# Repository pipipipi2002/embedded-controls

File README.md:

# The Hardware
- [Interactive BOM](https://pipipipi2002.github.io/embedded-controls/hardware/controls-carier-board/output/interactive_bom.html)

## MCU
This sensor module will require the STM32F446VETx Module from [stm32f446vetx-dev-module](https://github.com/pipipipi2002/stm32f446vetx-dev-module)

## Sensor
No | Sensor | Description | Connection
---| --- |--- | ---
1  | ICM-40609-D | 6-axis IMU | SPI1
2  | ICM-42688-P | 6-axis IMU | SPI3
3  | BNO085      | 9-axis IMU | SPI2
4  | BMP390      | Barometer  | SPI4

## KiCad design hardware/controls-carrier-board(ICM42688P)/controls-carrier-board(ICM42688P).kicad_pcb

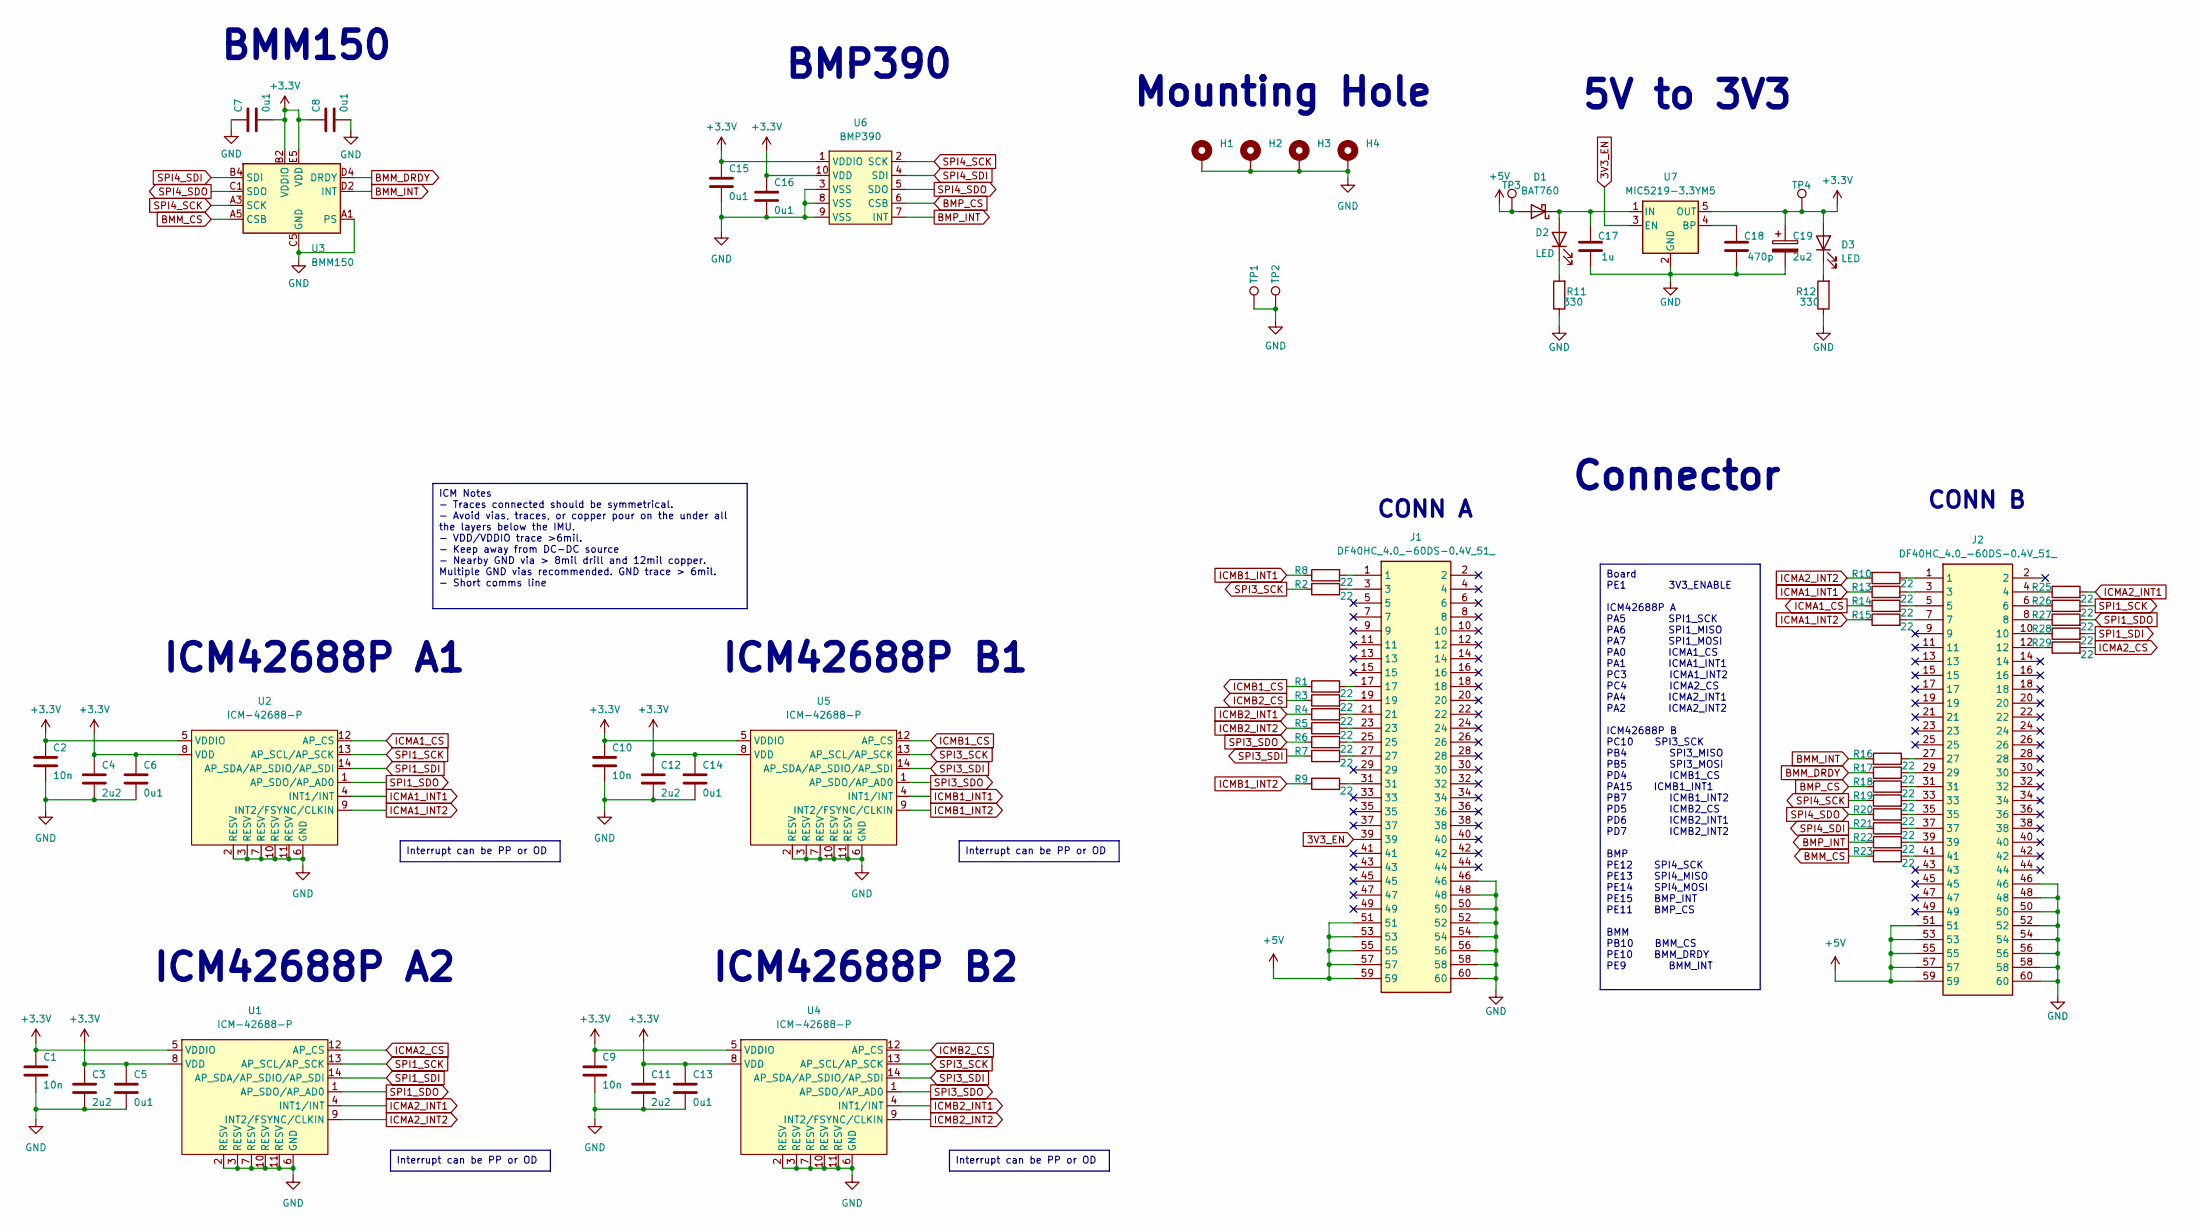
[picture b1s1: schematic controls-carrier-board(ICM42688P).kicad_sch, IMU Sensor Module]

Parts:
C1, C2, C9, C10: 10n; C_0402_1005Metric; JLCPCB C361206
C3, C4, C11, C12: 2u2; C_0402_1005Metric; JLCPCB C368595
C5, C6, C7, C8, C13, C14, C15, C16: 0u1; C_0402_1005Metric; JLCPCB C432917
C17: 1u; C_0603_1608Metric; JLCPCB C5673
C18: 470p; C_0603_1608Metric; JLCPCB C519409
C19: 2u2; CP_EIA-3216-18_Kemet-A_Pad1.58x1.35mm_HandSolder; JLCPCB C600494
D1: BAT760; D_SOD-323; JLCPCB C124187
D2, D3: LED; LED_0603_1608Metric; JLCPCB C131281
H1, H2, H3, H4: MountingHole_Pad; MountingHole_2.7mm_M2.5_Pad_Via
J1, J2: DF40HC_4.0_-60DS-0.4V_51_; DF40HC4060DS04V51; Mouser Part Number 798-DF4HC4060DS04V51
R1, R2, R3, R4, R5, R6, R7, R8, R9, R10, R13, R14, R15, R16, R17, R18, R19, R20, R21, R22, R23, R25, R26, R27, R28, R29: 22; R_0402_1005Metric; JLCPCB C413049
R11, R12: 330; R_0603_1608Metric; JLCPCB C441887
TP1, TP2, TP3, TP4: TestPoint; TestPoint_Keystone_5000-5004_Miniature
U1, U2, U4, U5: ICM-42688-P; ICM_LGA-14_3x2.5mm_P0.5mm; JLCPCB C1850418
U3: BMM150; WLCSP-12_1.56x1.56mm_P0.4mm; JLCPCB C171681
U6: BMP390; Bosch_LGA-10_2x2mm_P0.50mm; JLCPCB C9900016584
U7: MIC5219-3.3YM5; SOT-23-5; JLCPCB C29613

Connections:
3V3_EN: J1.39, U7.3 (EN)
+3.3V: C1.1, C2.1, C3.1, C4.1, C5.1, C6.1, C7.2, C8.1, C9.1, C10.1, C11.1, C12.1, C13.1, C14.1, C15.1, C16.1, C19.1, D3.2 (A), TP4.1, U1.5 (VDDIO), U1.8 (VDD), U2.5 (VDDIO), U2.8 (VDD), U3.B2 (VDDIO), U3.E5 (VDD), U4.5 (VDDIO), U4.8 (VDD), U5.5 (VDDIO), U5.8 (VDD), U6.1 (VDDIO), U6.10 (VDD), U7.5 (OUT)
+5V: D1.2 (A), J1.51, J1.53, J1.55, J1.57, J1.59, J2.51, J2.53, J2.55, J2.57, J2.59, TP3.1
BMM_CS: R23.1, U3.A5 (CSB)
BMM_DRDY: R17.1, U3.D4 (DRDY)
BMM_INT: R16.1, U3.D2 (INT)
BMP_CS: R18.1, U6.6 (CSB)
BMP_INT: R22.1, U6.7 (INT)
GND: C1.2, C2.2, C3.2, C4.2, C5.2, C6.2, C7.1, C8.2, C9.2, C10.2, C11.2, C12.2, C13.2, C14.2, C15.2, C16.2, C17.2, C18.2, C19.2, H1.1, H2.1, H3.1, H4.1, J1.46, J1.48, J1.50, J1.52, J1.54, J1.56, J1.58, J1.60, J2.46, J2.48, J2.50, J2.52, J2.54, J2.56, J2.58, J2.60, R11.1, R12.1, TP1.1, TP2.1, U1.2 (RESV), U1.3 (RESV), U1.6 (GND), U1.7 (RESV), U1.10 (RESV), U1.11 (RESV), U2.2 (RESV), U2.3 (RESV), U2.6 (GND), U2.7 (RESV), U2.10 (RESV), U2.11 (RESV), U3.A1 (PS), U3.C5 (GND), U3.E1 (GND), U3.E3 (GND), U4.2 (RESV), U4.3 (RESV), U4.6 (GND), U4.7 (RESV), U4.10 (RESV), U4.11 (RESV), U5.2 (RESV), U5.3 (RESV), U5.6 (GND), U5.7 (RESV), U5.10 (RESV), U5.11 (RESV), U6.3 (VSS), U6.8 (VSS), U6.9 (VSS), U7.2 (GND)
ICMA1_CS: R14.1, U2.12 (AP_CS)
ICMA1_INT1: R13.1, U2.4 (INT1/INT)
ICMA1_INT2: R15.1, U2.9 (INT2/FSYNC/CLKIN)
ICMA2_CS: R29.2, U1.12 (AP_CS)
ICMA2_INT1: R25.2, U1.4 (INT1/INT)
ICMA2_INT2: R10.2, U1.9 (INT2/FSYNC/CLKIN)
ICMB1_CS: R1.1, U5.12 (AP_CS)
ICMB1_INT1: R8.1, U5.4 (INT1/INT)
ICMB1_INT2: R9.1, U5.9 (INT2/FSYNC/CLKIN)
ICMB2_CS: R3.1, U4.12 (AP_CS)
ICMB2_INT1: R4.1, U4.4 (INT1/INT)
ICMB2_INT2: R5.1, U4.9 (INT2/FSYNC/CLKIN)
unnamed: C17.1, D1.1 (K), D2.2 (A), U7.1 (IN)
unnamed: D2.1 (K), R11.2
unnamed: D3.1 (K), R12.2
unnamed: J1.1, R8.2
unnamed: J1.3, R2.2
unnamed: J1.17, R1.2
unnamed: J1.19, R3.2
unnamed: J1.21, R4.2
unnamed: J1.23, R5.2
unnamed: J1.25, R6.2
unnamed: J1.27, R7.2
unnamed: J1.31, R9.2
unnamed: J2.1, R10.1
unnamed: J2.3, R13.2
unnamed: J2.4, R25.1
unnamed: J2.5, R14.2
unnamed: J2.6, R26.1
unnamed: J2.7, R15.2
unnamed: J2.8, R27.1
unnamed: J2.10, R28.1
unnamed: J2.12, R29.1
unnamed: J2.27, R16.2
unnamed: J2.29, R17.2
unnamed: J2.31, R18.2
unnamed: J2.33, R19.2
unnamed: J2.35, R20.2
unnamed: J2.37, R21.2
unnamed: J2.39, R22.2
unnamed: J2.41, R23.2
unnamed: C18.1, U7.4 (BP)
SPI1_SCK: R26.2, U1.13 (AP_SCL/AP_SCK), U2.13 (AP_SCL/AP_SCK)
SPI1_SDI: R28.2, U1.14 (AP_SDA/AP_SDIO/AP_SDI), U2.14 (AP_SDA/AP_SDIO/AP_SDI)
SPI1_SDO: R27.2, U1.1 (AP_SDO/AP_AD0), U2.1 (AP_SDO/AP_AD0)
SPI3_SCK: R2.1, U4.13 (AP_SCL/AP_SCK), U5.13 (AP_SCL/AP_SCK)
SPI3_SDI: R7.1, U4.14 (AP_SDA/AP_SDIO/AP_SDI), U5.14 (AP_SDA/AP_SDIO/AP_SDI)
SPI3_SDO: R6.1, U4.1 (AP_SDO/AP_AD0), U5.1 (AP_SDO/AP_AD0)
SPI4_SCK: R19.1, U3.A3 (SCK), U6.2 (SCK)
SPI4_SDI: R21.1, U3.B4 (SDI), U6.4 (SDI)
SPI4_SDO: R20.1, U3.C1 (SDO), U6.5 (SDO)

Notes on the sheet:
Board PE1 3V3_ENABLE ICM42688P A PA5 SPI1_SCK PA6 SPI1_MISO PA7 SPI1_MOSI PA0 ICMA1_CS PA1 ICMA1_INT1 PC3 ICMA1_INT2 PC4 ICMA2_CS PA4 ICMA2_INT1 PA2 ICMA2_INT2 ICM42688P B PC10 SPI3_SCK PB4 SPI3_MISO PB5 SPI3_MOSI PD4 ICMB1_CS PA15 ICMB1_INT1 PB7 ICMB1_INT2 PD5 ICMB2_CS PD6 ICMB2_INT1 PD7 ICMB2_INT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
ICM Notes - Traces connected should be symmetrical. - Avoid vias, traces, or copper pour on the under all the layers below the IMU. - VDD/VDDIO trace >6mil. - Keep away from DC-DC source - Nearby GND via > 8mil drill and 12mil copper. Multiple GND vias recommended. GND trace > 6mil. - Short comms l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
Interrupt can be PP or OD
Connector
5V to 3V3
BMM150
ICM42688P B1
Mounting Hole
ICM42688P A2
ICM42688P B2
BMP390
CONN A
ICM42688P A1
CONN B

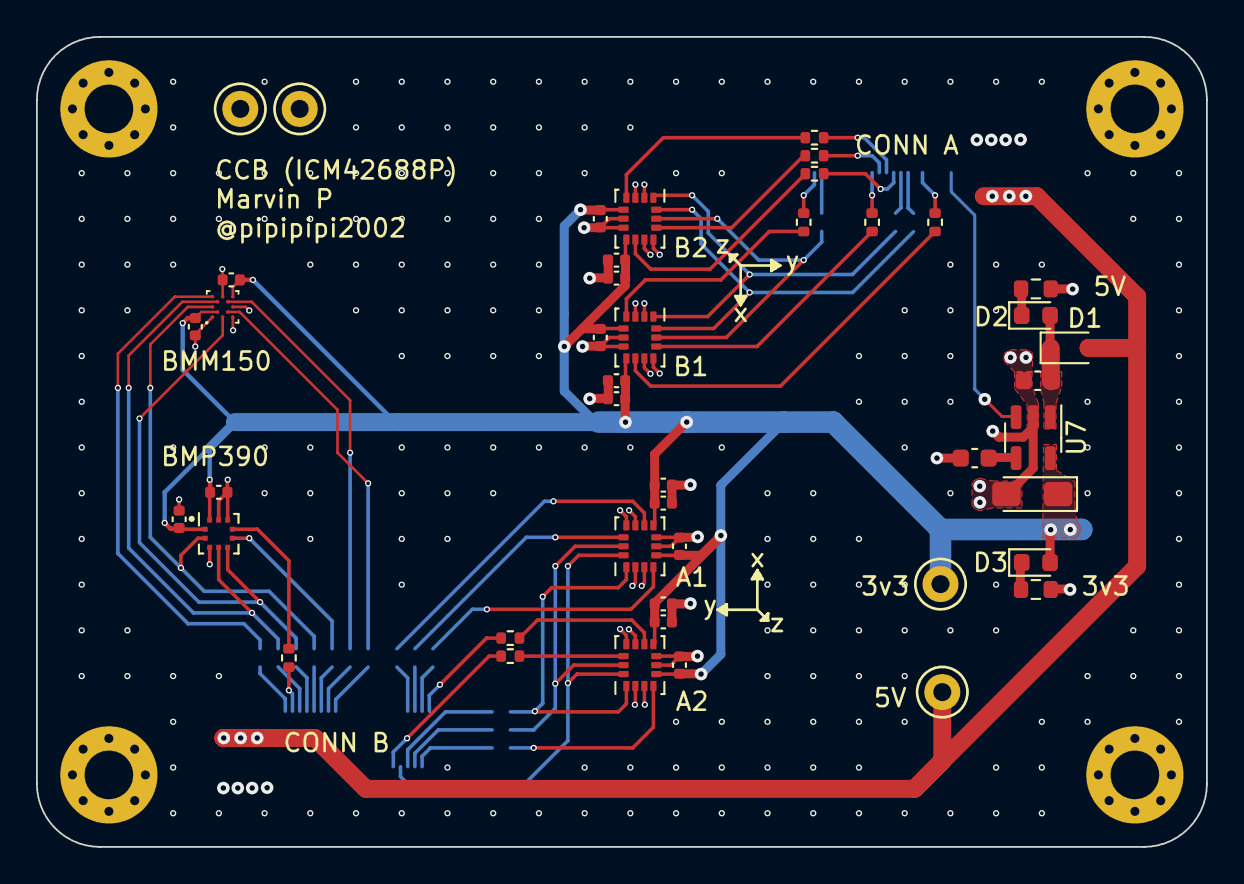
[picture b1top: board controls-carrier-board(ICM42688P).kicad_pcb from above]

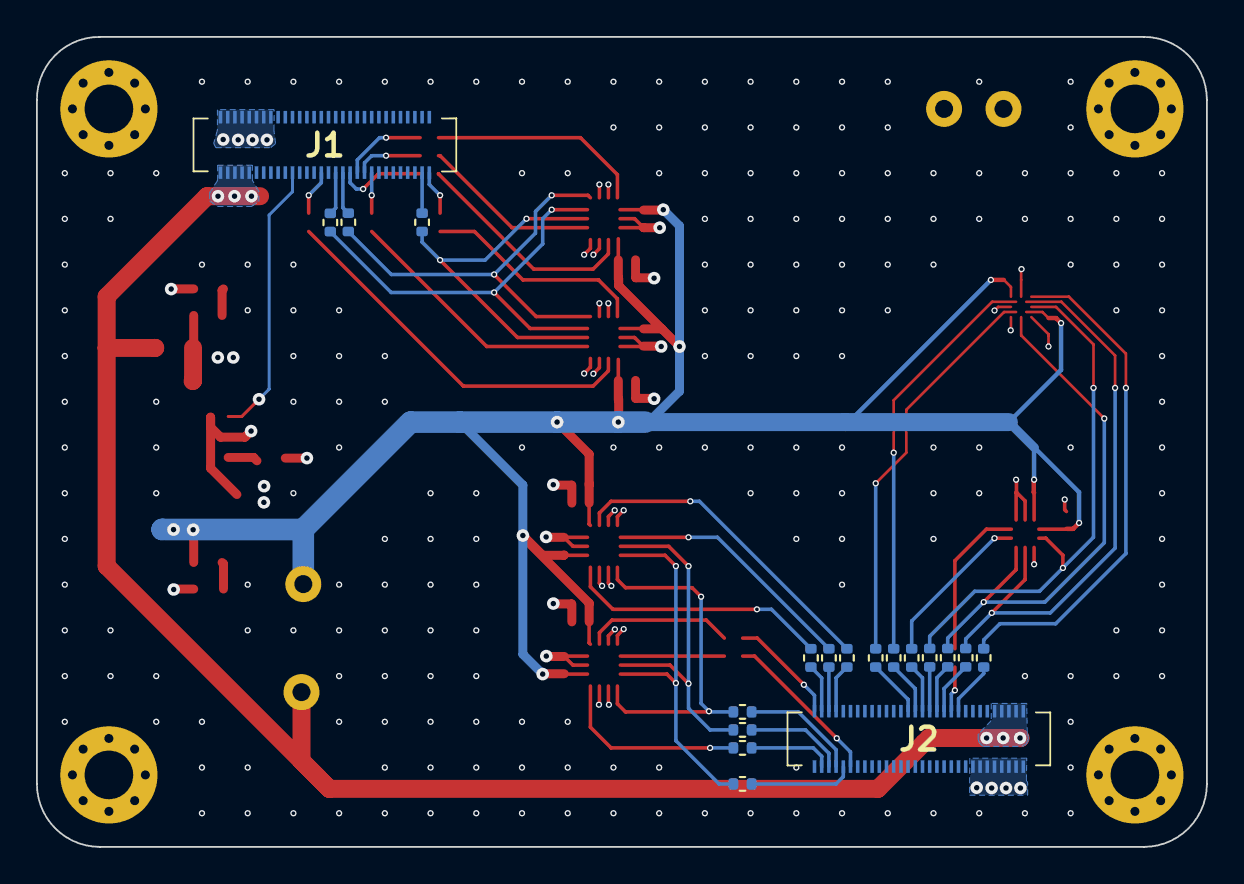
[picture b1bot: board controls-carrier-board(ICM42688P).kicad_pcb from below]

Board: 4 copper layers, 65.0 x 45.0 mm, 67 parts (19 on the bottom side), 60 nets.

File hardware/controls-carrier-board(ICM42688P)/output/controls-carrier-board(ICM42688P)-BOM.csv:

Comment,Designator,Footprint,LCSC
"10n","C1,C2,C9,C10","Capacitor_SMD:C_0402_1005Metric","C361206"
"1u","C17","Capacitor_SMD:C_0603_1608Metric","C5673"
"470p","C18","Capacitor_SMD:C_0603_1608Metric","C519409"
"2u2","C19","Capacitor_Tantalum_SMD:CP_EIA-3216-18_Kemet-A_Pad1.58x1.35mm_HandSolder","C600494"
"2u2","C3,C4,C11,C12","Capacitor_SMD:C_0402_1005Metric","C368595"
"0u1","C5,C6,C7,C8,C13,C14,C15,C16","Capacitor_SMD:C_0402_1005Metric","C432917"
"BAT760","D1","Diode_SMD:D_SOD-323","C124187"
"LED","D2,D3","LED_SMD:LED_0603_1608Metric","C131281"
"DF40HC_4.0_-60DS-0.4V_51_","J1,J2","whose_lib:DF40HC4060DS04V51","C3647944"
"22","R1,R2,R3,R4,R5,R6,R7,R8,R9,R10,R13,R14,R15,R16,R17,R18,R19,R20,R21,R22,R23,R25,R26,R27,R28,R29","Resistor_SMD:R_0402_1005Metric","C413049"
"330","R11,R12","Resistor_SMD:R_0603_1608Metric","C441887"
"ICM-42688-P","U1,U2,U4,U5","whose_lib:ICM_LGA-14_3x2.5mm_P0.5mm","C1850418"
"BMM150","U3","Package_CSP:WLCSP-12_1.56x1.56mm_P0.4mm","C171681"
"BMP390","U6","whose_lib:Bosch_LGA-10_2x2mm_P0.50mm","C9900016584"
"MIC5219-3.3YM5","U7","Package_TO_SOT_SMD:SOT-23-5","C29613"

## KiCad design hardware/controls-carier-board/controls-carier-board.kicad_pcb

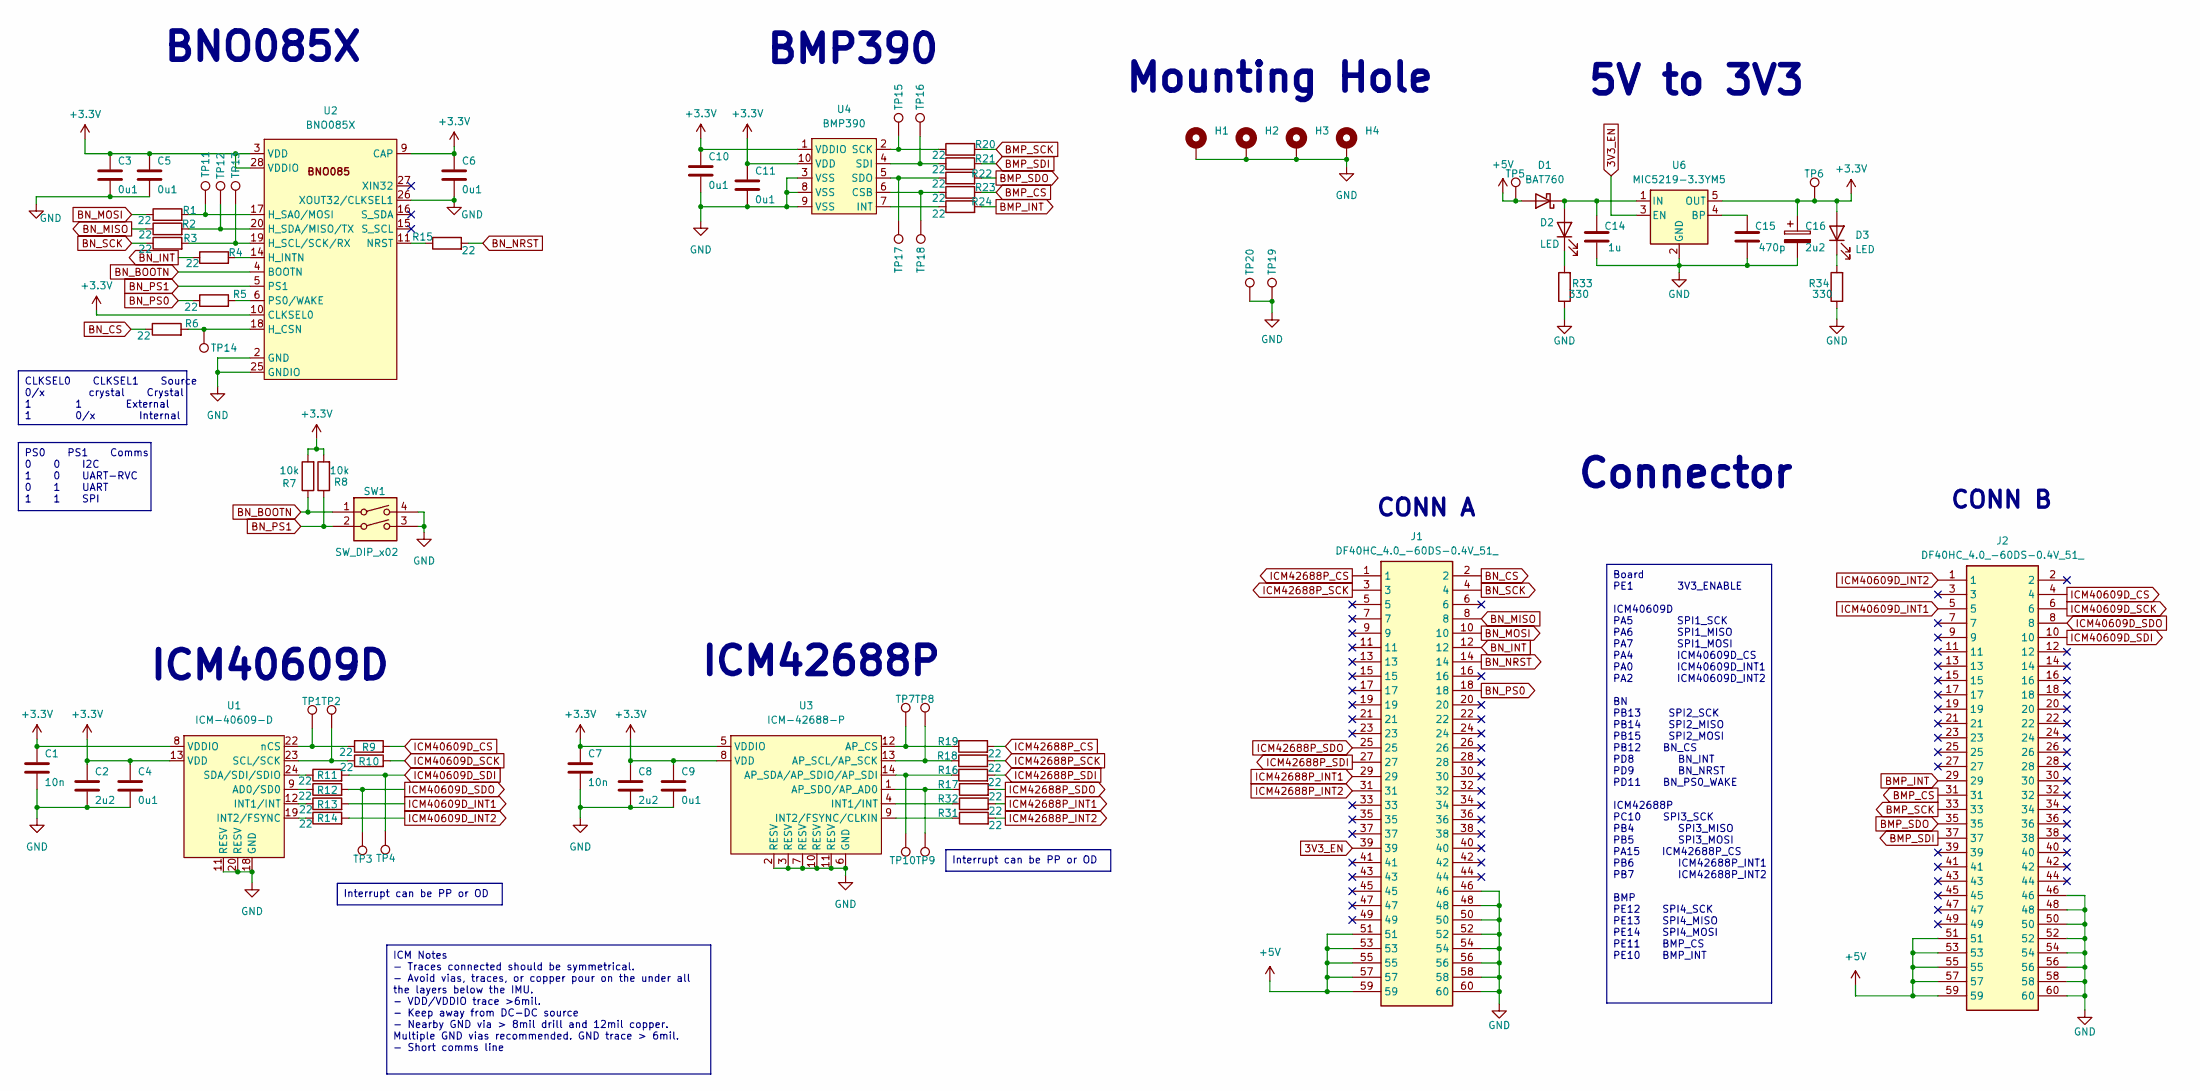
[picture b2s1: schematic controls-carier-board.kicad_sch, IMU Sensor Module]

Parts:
C1, C7: 10n; C_0603_1608Metric; JLCPCB C307346
C2, C8: 2u2; C_0603_1608Metric; JLCPCB C100082
C3, C4, C5, C6, C9, C10, C11: 0u1; C_0603_1608Metric; JLCPCB C1591
C14: 1u; C_0603_1608Metric; JLCPCB C5673
C15: 470p; C_0603_1608Metric; JLCPCB C519409
C16: 2u2; CP_EIA-3216-18_Kemet-A_Pad1.58x1.35mm_HandSolder; JLCPCB C600494
D1: BAT760; D_SOD-323; JLCPCB C124187
D2, D3: LED; LED_0603_1608Metric; JLCPCB C131281
H1, H2, H3, H4: MountingHole_Pad; MountingHole_2.7mm_M2.5_Pad_Via
J1, J2: DF40HC_4.0_-60DS-0.4V_51_; DF40HC4060DS04V51; Mouser Part Number 798-DF4HC4060DS04V51
R1, R2, R3, R4, R5, R6, R9, R10, R11, R12, R13, R14, R15, R16, R17, R18, R19, R20, R21, R22, R23, R24, R31, R32: 22; R_0603_1608Metric; JLCPCB C491194
R7, R8: 10k; R_0603_1608Metric; JLCPCB C98220
R33, R34: 330; R_0603_1608Metric; JLCPCB C441887
SW1: SW_DIP_x02; 218-2LPSTRF; JLCPCB C314498
TP1, TP2, TP3, TP4, TP5, TP6, TP7, TP8, TP9, TP10, TP11, TP12, TP13, TP14, TP15, TP16, TP17, TP18, TP19, TP20: TestPoint; TestPoint_Keystone_5000-5004_Miniature
U1: ICM-40609-D; ICM_LGA-24_3x3mm-P0.4mm; JLCPCB C5360621
U2: BNO085X; LGA-28_5.2x3.8mm_P0.5mm; JLCPCB C5189642
U3: ICM-42688-P; ICM_LGA-14_3x2.5mm_P0.5mm; JLCPCB C1850418
U4: BMP390; Bosch_LGA-10_2x2mm_P0.50mm; JLCPCB C9900016584
U6: MIC5219-3.3YM5; SOT-23-5; JLCPCB C29613

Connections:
3V3_EN: J1.39, U6.3 (EN)
+3.3V: C1.1, C2.1, C3.1, C4.1, C5.1, C6.1, C7.1, C8.1, C9.1, C10.1, C11.1, C16.1, D3.2 (A), R7.2, R8.2, TP6.1, U1.8 (VDDIO), U1.13 (VDD), U2.3 (VDD), U2.9 (CAP), U2.10 (CLKSEL0), U2.28 (VDDIO), U3.5 (VDDIO), U3.8 (VDD), U4.1 (VDDIO), U4.10 (VDD), U6.5 (OUT)
+5V: D1.2 (A), J1.51, J1.53, J1.55, J1.57, J1.59, J2.51, J2.53, J2.55, J2.57, J2.59, TP5.1
BMP_CS: J2.31, R23.2
BMP_INT: J2.29, R24.2
BMP_SCK: J2.33, R20.2
BMP_SDI: J2.37, R21.2
BMP_SDO: J2.35, R22.2
BN_BOOTN: R7.1, SW1.1, U2.4 (BOOTN)
BN_CS: J1.2, R6.1
BN_INT: J1.12, R4.1
BN_MISO: J1.8, R2.1
BN_MOSI: J1.10, R1.1
BN_NRST: J1.14, R15.2
BN_PS0: J1.18, R5.1
BN_PS1: R8.1, SW1.2, U2.5 (PS1)
BN_SCK: J1.4, R3.1
GND: C1.2, C2.2, C3.2, C4.2, C5.2, C6.2, C7.2, C8.2, C9.2, C10.2, C11.2, C14.2, C15.2, C16.2, H1.1, H2.1, H3.1, H4.1, J1.46, J1.48, J1.50, J1.52, J1.54, J1.56, J1.58, J1.60, J2.46, J2.48, J2.50, J2.52, J2.54, J2.56, J2.58, J2.60, R33.1, R34.1, SW1.3, SW1.4, TP19.1, TP20.1, U1.11 (RESV), U1.18 (GND), U1.20 (RESV), U2.2 (GND), U2.25 (GNDIO), U2.26 (XOUT32/CLKSEL1), U3.2 (RESV), U3.3 (RESV), U3.6 (GND), U3.7 (RESV), U3.10 (RESV), U3.11 (RESV), U4.3 (VSS), U4.8 (VSS), U4.9 (VSS), U6.2 (GND)
ICM40609D_CS: J2.4, R9.2
ICM40609D_INT1: J2.5, R13.2
ICM40609D_INT2: J2.1, R14.2
ICM40609D_SCK: J2.6, R10.2
ICM40609D_SDI: J2.10, R11.2, TP4.1
ICM40609D_SDO: J2.8, R12.2, TP3.1
ICM42688P_CS: J1.1, R19.2
ICM42688P_INT1: J1.29, R32.2
ICM42688P_INT2: J1.31, R31.2
ICM42688P_SCK: J1.3, R18.2
ICM42688P_SDI: J1.27, R16.2
ICM42688P_SDO: J1.25, R17.2
unnamed: C14.1, D1.1 (K), D2.2 (A), U6.1 (IN)
unnamed: D2.1 (K), R33.2
unnamed: D3.1 (K), R34.2
unnamed: R12.1, U1.9 (AD0/SD0)
unnamed: R13.1, U1.12 (INT1/INT)
unnamed: R14.1, U1.19 (INT2/FSYNC)
unnamed: R10.1, TP2.1, U1.23 (SCL/SCK)
unnamed: R11.1, U1.24 (SDA/SDI/SDIO)
unnamed: R9.1, TP1.1, U1.22 (nCS)
unnamed: R6.2, TP14.1, U2.18 (H_CSN)
unnamed: R4.2, U2.14 (H_INTN)
unnamed: R1.2, TP11.1, U2.17 (H_SA0/MOSI)
unnamed: R3.2, TP13.1, U2.19 (H_SCL/SCK/RX)
unnamed: R2.2, TP12.1, U2.20 (H_SDA/MISO/TX)
unnamed: R15.1, U2.11 (NRST)
unnamed: R5.2, U2.6 (PS0/WAKE)
unnamed: R19.1, TP7.1, U3.12 (AP_CS)
unnamed: R18.1, TP8.1, U3.13 (AP_SCL/AP_SCK)
unnamed: R16.1, TP10.1, U3.14 (AP_SDA/AP_SDIO/AP_SDI)
unnamed: R17.1, TP9.1, U3.1 (AP_SDO/AP_AD0)
unnamed: R32.1, U3.4 (INT1/INT)
unnamed: R31.1, U3.9 (INT2/FSYNC/CLKIN)
unnamed: R23.1, TP18.1, U4.6 (CSB)
unnamed: R24.1, U4.7 (INT)
unnamed: R20.1, TP15.1, U4.2 (SCK)
unnamed: R21.1, TP16.1, U4.4 (SDI)
unnamed: R22.1, TP17.1, U4.5 (SDO)
unnamed: C15.1, U6.4 (BP)

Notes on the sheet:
Board PE1 3V3_ENABLE ICM40609D PA5 SPI1_SCK PA6 SPI1_MISO PA7 SPI1_MOSI PA4 ICM40609D_CS PA0 ICM40609D_INT1 PA2 ICM40609D_INT2 BN PB13 SPI2_SCK PB14 SPI2_MISO PB15 SPI2_MOSI PB12 BN_CS PD8 BN_INT PD9 BN_NRST PD11 BN_PS0_WAKE ICM42688P PC10 SPI3_SCK PB4 SPI3_MISO PB5 SPI3_MOSI PA15 ICM42688P_CS PB6 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
CLKSEL0 CLKSEL1 Source 0/x crystal Crystal 1 1 External 1 0/x Internal
ICM Notes - Traces connected should be symmetrical. - Avoid vias, traces, or copper pour on the under all the layers below the IMU. - VDD/VDDIO trace >6mil. - Keep away from DC-DC source - Nearby GND via > 8mil drill and 12mil copper. Multiple GND vias recommended. GND trace > 6mil. - Short comms l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
Interrupt can be PP or OD
PS0 PS1 Comms 0 0 I2C 1 0 UART-RVC 0 1 UART 1 1 SPI
Connector
5V to 3V3
ICM42688P
Mounting Hole
BMP390
CONN A
BNO085X
CONN B
ICM40609D

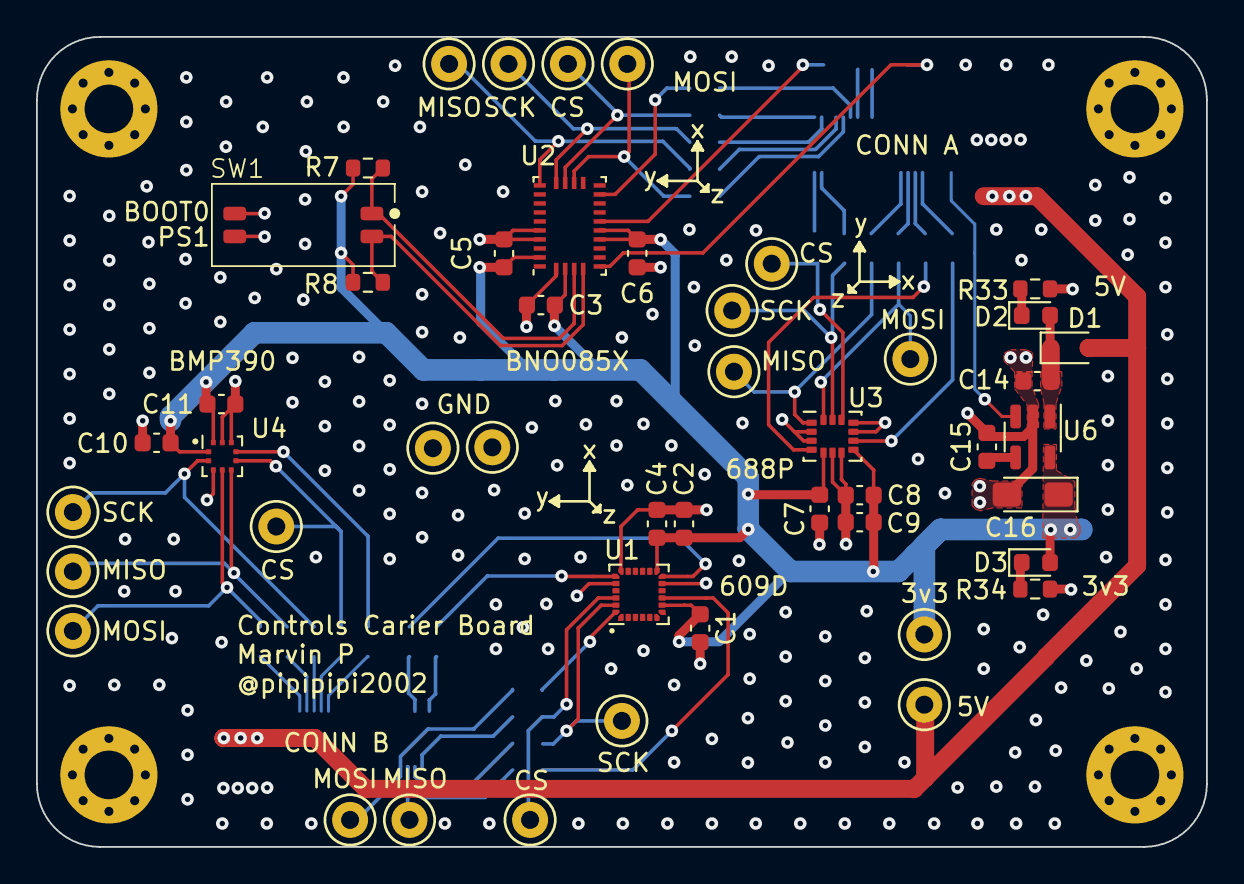
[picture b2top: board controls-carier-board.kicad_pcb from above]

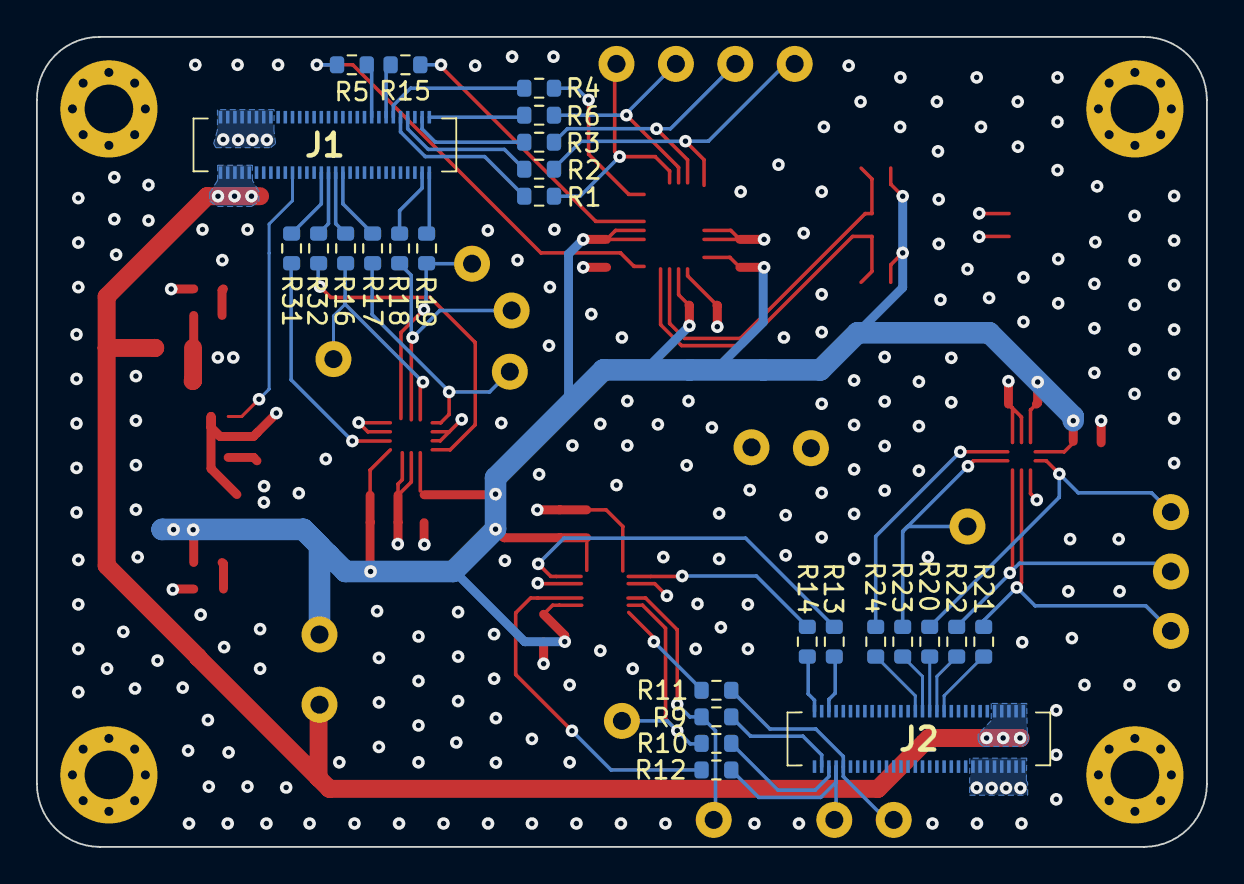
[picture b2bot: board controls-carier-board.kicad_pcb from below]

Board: 4 copper layers, 65.0 x 45.0 mm, 77 parts (26 on the bottom side), 58 nets.

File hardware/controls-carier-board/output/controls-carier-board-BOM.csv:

Comment,Designator,Footprint,LCSC
"10n","C1,C7","Capacitor_SMD:C_0603_1608Metric","C307346"
"1u","C14","Capacitor_SMD:C_0603_1608Metric","C5673"
"470p","C15","Capacitor_SMD:C_0603_1608Metric","C519409"
"2u2","C16","Capacitor_Tantalum_SMD:CP_EIA-3216-18_Kemet-A_Pad1.58x1.35mm_HandSolder","C600494"
"2u2","C2,C8","Capacitor_SMD:C_0603_1608Metric","C100082"
"0u1","C3,C4,C5,C6,C9,C10,C11","Capacitor_SMD:C_0603_1608Metric","C1591"
"BAT760","D1","Diode_SMD:D_SOD-323","C124187"
"LED","D2,D3","LED_SMD:LED_0603_1608Metric","C131281"
"DF40HC_4.0_-60DS-0.4V_51_","J1,J2","whose_lib:DF40HC4060DS04V51","C3647944"
"22","R1,R2,R3,R4,R5,R6,R9,R10,R11,R12,R13,R14,R15,R16,R17,R18,R19,R20,R21,R22,R23,R24,R31,R32","Resistor_SMD:R_0603_1608Metric","C491194"
"330","R33,R34","Resistor_SMD:R_0603_1608Metric","C441887"
"10k","R7,R8","Resistor_SMD:R_0603_1608Metric","C98220"
"SW_DIP_x02","SW1","whose_lib:218-2LPSTRF","C314498"
"ICM-40609-D","U1","whose_lib:ICM_LGA-24_3x3mm-P0.4mm","C5360621"
"BNO085X","U2","Package_LGA:LGA-28_5.2x3.8mm_P0.5mm","C5189642"
"ICM-42688-P","U3","whose_lib:ICM_LGA-14_3x2.5mm_P0.5mm","C1850418"
"BMP390","U4","whose_lib:Bosch_LGA-10_2x2mm_P0.50mm","C9900016584"
"MIC5219-3.3YM5","U6","Package_TO_SOT_SMD:SOT-23-5","C29613"

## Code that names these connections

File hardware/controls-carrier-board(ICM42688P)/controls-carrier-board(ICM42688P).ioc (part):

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Mcu.Name=STM32F446V(C-E)Tx
Mcu.Package=LQFP100
Mcu.UserName=STM32F446VETx
PA0-WKUP.GPIOParameters=GPIO_Label
PA0-WKUP.GPIO_Label=ICMA1_CS
PA0-WKUP.Signal=GPIO_Input
PA1.GPIOParameters=GPIO_Label
PA1.GPIO_Label=ICMA1_INT1
PA1.Signal=GPIO_Input
PA13.Mode=Trace_Asynchronous_SW
PA13.Signal=SYS_JTMS-SWDIO
PA14.Mode=Trace_Asynchronous_SW
PA14.Signal=SYS_JTCK-SWCLK
PA15.GPIOParameters=GPIO_Label
PA15.GPIO_Label=ICMB1_INT1
PA15.Signal=GPIO_Input
PA2.GPIOParameters=GPIO_Label
PA2.GPIO_Label=ICMA2_INT2
PA2.Signal=GPIO_Input
PA4.GPIOParameters=GPIO_Label
PA4.GPIO_Label=ICMA2_INT1
PA4.Signal=GPIO_Output
PA5.Mode=Full_Duplex_Master
PA5.Signal=SPI1_SCK
PA6.Mode=Full_Duplex_Master
PA6.Signal=SPI1_MISO
PA7.Mode=Full_Duplex_Master
PA7.Signal=SPI1_MOSI
PB1.Signal=SDIO_D2
PB10.GPIOParameters=GPIO_Label
PB10.GPIO_Label=BMM_CS
PB10.Signal=GPIO_Input
PB2.Signal=SDIO_CK
PB3.Mode=Trace_Asynchronous_SW
PB3.Signal=SYS_JTDO-SWO
PB4.Mode=Full_Duplex_Master
PB4.Signal=SPI3_MISO
PB5.Mode=Full_Duplex_Master
PB5.Signal=SPI3_MOSI
PB7.GPIOParameters=GPIO_Label
PB7.GPIO_Label=ICMB1_INT2
PB7.Signal=GPIO_Input
PB8.Signal=CAN1_RX
PB9.Signal=CAN1_TX
PC10.Mode=Full_Duplex_Master
PC10.Signal=SPI3_SCK
PC11.Signal=SDIO_D3
PC14-OSC32_IN.Mode=LSE-External-Oscillator
PC14-OSC32_IN.Signal=RCC_OSC32_IN
PC15-OSC32_OUT.Mode=LSE-External-Oscillator
PC15-OSC32_OUT.Signal=RCC_OSC32_OUT
PC3.GPIOParameters=GPIO_Label
PC3.GPIO_Label=ICMA1_INT2
PC3.Signal=GPIO_Input
PC4.GPIOParameters=GPIO_Label
PC4.GPIO_Label=ICMA2_CS
PC4.Signal=GPIO_Output
PC8.Signal=SDIO_D0
PC9.Signal=SDIO_D1
PD10.GPIOParameters=GPIO_Label
PD10.GPIO_Label=SDIO_nDET
PD10.Signal=GPIO_Input
PD2.Signal=SDIO_CMD
PD4.GPIOParameters=GPIO_Label
PD4.GPIO_Label=ICMB1_CS
PD4.Signal=GPIO_Output
PD5.GPIOParameters=GPIO_Label
PD5.GPIO_Label=ICMB2_CS
PD5.Signal=GPIO_Output
PD6.GPIOParameters=GPIO_Label
PD6.GPIO_Label=ICMB2_INT1
PD6.Signal=GPIO_Input
PD7.GPIOParameters=GPIO_Label
PD7.GPIO_Label=ICMB2_INT2
PD7.Signal=GPIO_Input
PE1.GPIOParameters=GPIO_PuPd,GPIO_Label
PE1.GPIO_Label=EN_3V3
PE1.GPIO_PuPd=GPIO_PULLDOWN
PE1.Signal=GPIO_Output
PE10.GPIOParameters=GPIO_Label
PE10.GPIO_Label=BMM_DRDY
PE10.Signal=GPIO_Input
PE11.GPIOParameters=GPIO_Label
PE11.GPIO_Label=BMP_CS
PE11.Signal=GPIO_Output
PE12.Mode=Full_Duplex_Master
PE12.Signal=SPI4_SCK
PE13.Mode=Full_Duplex_Master
PE13.Signal=SPI4_MISO
PE14.Mode=Full_Duplex_Master
PE14.Signal=SPI4_MOSI
PE15.GPIOParameters=GPIO_Label
PE15.GPIO_Label=BMP_INT
PE15.Signal=GPIO_Output
PE3.GPIOParameters=GPIO_Label
PE3.GPIO_Label=GP_LED
PE3.Signal=GPIO_Output
PE7.Mode=Asynchronous
PE7.Signal=UART5_RX
PE8.Mode=Asynchronous
PE8.Signal=UART5_TX
PE9.GPIOParameters=GPIO_Label
PE9.GPIO_Label=BMM_INT
PE9.Signal=GPIO_Input
PH0-OSC_IN.Mode=HSE-External-Oscillator
PH0-OSC_IN.Signal=RCC_OSC_IN
PH1-OSC_OUT.Mode=HSE-External-Oscillator
PH1-OSC_OUT.Signal=RCC_OSC_OUT
RCC.HSE_VALUE=20000000
RCC.SYSCLKFreq_VALUE=168000000
RCC.SYSCLKSource=RCC_SYSCLKSOURCE_PLLCLK
board=custom

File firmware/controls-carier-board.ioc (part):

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Mcu.Name=STM32F446V(C-E)Tx
Mcu.Package=LQFP100
Mcu.UserName=STM32F446VETx
PA0-WKUP.GPIOParameters=GPIO_Label
PA0-WKUP.GPIO_Label=ICM40609D_INT1
PA0-WKUP.Signal=GPIO_Input
PA13.Mode=Trace_Asynchronous_SW
PA13.Signal=SYS_JTMS-SWDIO
PA14.Mode=Trace_Asynchronous_SW
PA14.Signal=SYS_JTCK-SWCLK
PA15.GPIOParameters=GPIO_Label
PA15.GPIO_Label=ICM42688P_CS
PA15.Signal=GPIO_Output
PA2.GPIOParameters=GPIO_Label
PA2.GPIO_Label=ICM40609D_INT2
PA2.Signal=GPIO_Input
PA4.GPIOParameters=GPIO_Label
PA4.GPIO_Label=ICM40609D_CS
PA4.Signal=GPIO_Output
PA5.Mode=Full_Duplex_Master
PA5.Signal=SPI1_SCK
PA6.Mode=Full_Duplex_Master
PA6.Signal=SPI1_MISO
PA7.Mode=Full_Duplex_Master
PA7.Signal=SPI1_MOSI
PB1.Signal=SDIO_D2
PB12.GPIOParameters=GPIO_Speed,GPIO_Label
PB12.GPIO_Label=BN_CS
PB12.GPIO_Speed=GPIO_SPEED_FREQ_VERY_HIGH
PB12.Signal=GPIO_Output
PB13.Mode=Full_Duplex_Master
PB13.Signal=SPI2_SCK
PB14.Mode=Full_Duplex_Master
PB14.Signal=SPI2_MISO
PB15.Mode=Full_Duplex_Master
PB15.Signal=SPI2_MOSI
PB2.Signal=SDIO_CK
PB3.Mode=Trace_Asynchronous_SW
PB3.Signal=SYS_JTDO-SWO
PB4.Mode=Full_Duplex_Master
PB4.Signal=SPI3_MISO
PB5.Mode=Full_Duplex_Master
PB5.Signal=SPI3_MOSI
PB6.GPIOParameters=GPIO_Label
PB6.GPIO_Label=ICM42688P_INT1
PB6.Signal=GPIO_Input
PB7.GPIOParameters=GPIO_Label
PB7.GPIO_Label=ICM42688P_INT2
PB7.Signal=GPIO_Input
PB8.Signal=CAN1_RX
PB9.Signal=CAN1_TX
PC10.Mode=Full_Duplex_Master
PC10.Signal=SPI3_SCK
PC11.Signal=SDIO_D3
PC14-OSC32_IN.Mode=LSE-External-Oscillator
PC14-OSC32_IN.Signal=RCC_OSC32_IN
PC15-OSC32_OUT.Mode=LSE-External-Oscillator
PC15-OSC32_OUT.Signal=RCC_OSC32_OUT
PC8.Signal=SDIO_D0
PC9.Signal=SDIO_D1
PD10.GPIOParameters=GPIO_Label
PD10.GPIO_Label=SDIO_nDET
PD10.Signal=GPIO_Input
PD11.GPIOParameters=GPIO_Speed,GPIO_Label
PD11.GPIO_Label=BN_PS0_WAKE
PD11.GPIO_Speed=GPIO_SPEED_FREQ_VERY_HIGH
PD11.Signal=GPIO_Output
PD2.Signal=SDIO_CMD
PD8.GPIOParameters=GPIO_PuPd,GPIO_Label
PD8.GPIO_Label=BN_INT
PD8.GPIO_PuPd=GPIO_PULLUP
PD8.Signal=GPIO_Input
PD9.GPIOParameters=GPIO_Speed,GPIO_Label
PD9.GPIO_Label=BN_NRST
PD9.GPIO_Speed=GPIO_SPEED_FREQ_VERY_HIGH
PD9.Signal=GPIO_Output
PE1.GPIOParameters=GPIO_PuPd,GPIO_Label
PE1.GPIO_Label=EN_3V3
PE1.GPIO_PuPd=GPIO_PULLDOWN
PE1.Signal=GPIO_Output
PE10.GPIOParameters=GPIO_Label
PE10.GPIO_Label=BMP_INT
PE10.Signal=GPIO_Input
PE11.GPIOParameters=GPIO_Label
PE11.GPIO_Label=BMP_CS
PE11.Signal=GPIO_Output
PE12.Mode=Full_Duplex_Master
PE12.Signal=SPI4_SCK
PE13.Mode=Full_Duplex_Master
PE13.Signal=SPI4_MISO
PE14.Mode=Full_Duplex_Master
PE14.Signal=SPI4_MOSI
PE3.GPIOParameters=GPIO_Label
PE3.GPIO_Label=GP_LED
PE3.Signal=GPIO_Output
PE7.Mode=Asynchronous
PE7.Signal=UART5_RX
PE8.Mode=Asynchronous
PE8.Signal=UART5_TX
PH0-OSC_IN.Mode=HSE-External-Oscillator
PH0-OSC_IN.Signal=RCC_OSC_IN
PH1-OSC_OUT.Mode=HSE-External-Oscillator
PH1-OSC_OUT.Signal=RCC_OSC_OUT
RCC.HSE_VALUE=20000000
RCC.SYSCLKFreq_VALUE=168000000
RCC.SYSCLKSource=RCC_SYSCLKSOURCE_PLLCLK
board=custom

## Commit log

2024-01-29 fab version
2024-01-29 added bom
2024-01-30 basic setup and bringup from CubeMX
2024-01-31 more decent cmake workflow
2024-01-31 Update makefile and tasks for stflash
2024-01-31 add docs
2024-01-31 edit docs
2024-02-01 sync project
2024-02-17 added 3d print files
2024-02-17 Exploding view
2024-02-24 basic setup completed
2024-02-25 fix: update SPI baud rate prescaler and clock phase/polarity for SPI1, SPI2, SPI3, and SPI4
2024-02-26 basic setup for BN copied
2024-02-26 feat: partial code implemented
2024-02-28 feat/impl good
2024-02-29 Change name
2024-02-29 Not working
2024-02-29 without LL but from the korean dude files
2024-02-29 This works too but its sus
    The code works without being uploaded with the HAL_firmware
2024-02-29 Working library
2024-02-29 add template for BN-SHTP
2024-03-02 Added regs list for ICM42688P
2024-03-02 baby steps
2024-03-04 working
2024-03-04 Added calibration codes
2024-03-04 Fix bugs
2024-03-04 add error handler
2024-03-04 Fix enable bug
2024-03-05 edit variable name
2024-03-07 Decouple ICM42688P and ICM40609D with ICM_driver as main library
2024-03-07 Rename lib
2024-03-07 Remove redundant buffer
2024-03-07 Tested on boards
2024-03-07 update linker options
2024-03-07 Switch printf to own fork
2024-03-07 new printf fork implemented and tested
2024-03-09 Added matlab integration
2024-07-28 cleanup
2024-07-30 Added ICM42688P version
